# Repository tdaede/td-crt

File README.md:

# td-crt

This repo contains work-in-progress electronics to control a CRT monitor (aka a CRT chassis).

It is divided up into several separate projects, as follows:

* **[td-deflect](td-deflect/)** - Main PCB, containing microcontroller, horizontal and vertical deflection circuits, RGB amplifier, B+ power supply, 12V and -12V power supplies, and heater power supply. Functional with an enormous amount of rework.

* **[td-hv](td-hv/)** - Regulated HV/focus/screen power supply, based on K7000 clone flyback. Currently marginally functional, demos were done with the original monitor's HV.

* **[td-rgbinput](td-rgbinput/)** - Poorly named RGB amplifier that replaces the version on td-deflect, using more modern parts. Currently untested.

* **[td-180v](td-180v/)** - 180V (and heater) boost converter, designed to be installed on a neck board to provide an optional dedicated power supply for the cathode amplifiers.

* **[td-rgb](td-rgb/)** - Old RGB mod PCB, I should move it to a separate repo at some point.

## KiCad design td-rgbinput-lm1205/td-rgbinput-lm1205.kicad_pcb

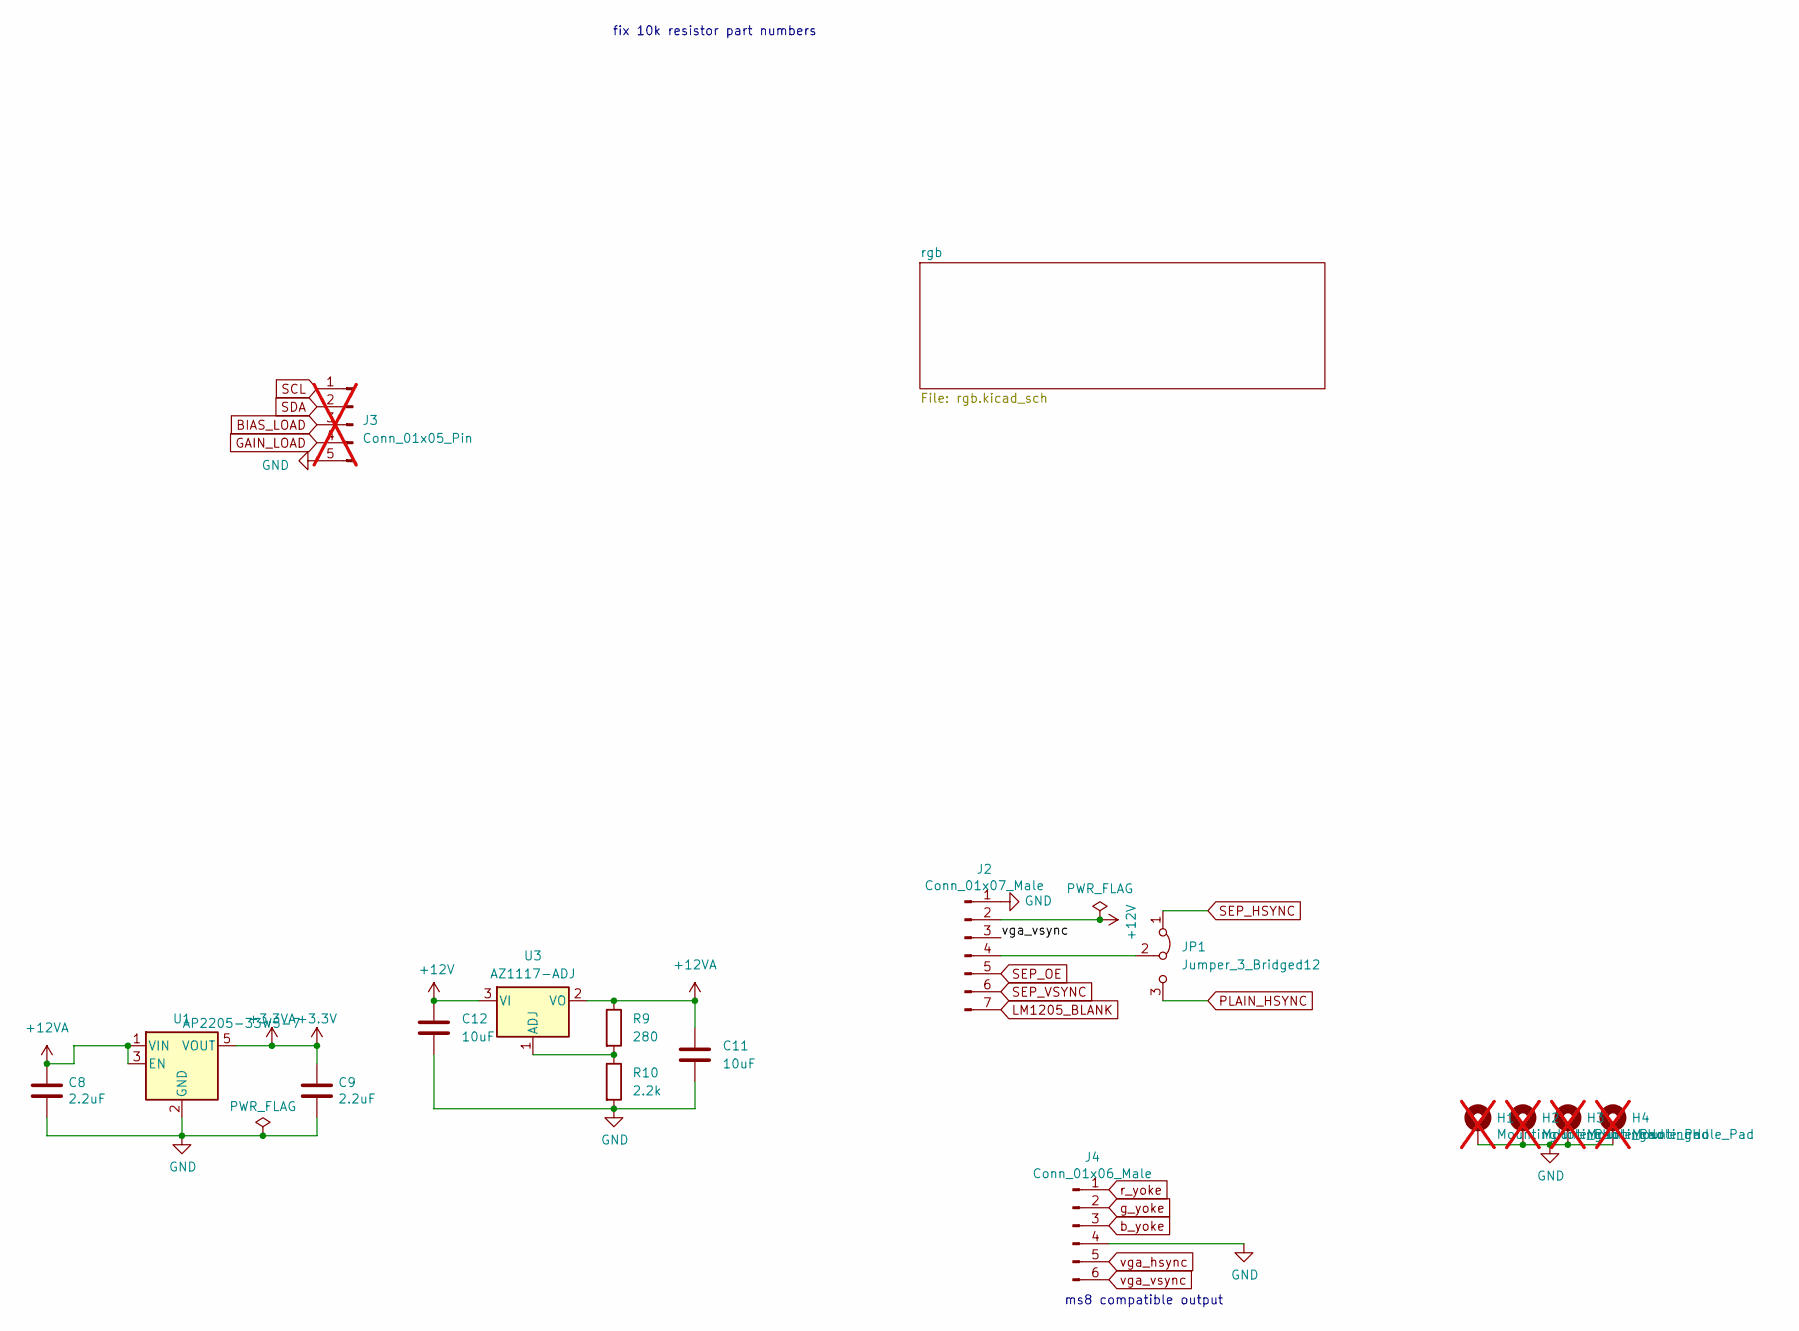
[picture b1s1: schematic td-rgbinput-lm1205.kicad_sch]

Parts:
C8, C9: 2.2uF; C_0805_2012Metric; Digikey 490-14467-1-ND
C11, C12: 10uF; C_0805_2012Metric; Digikey 490-10516-1-ND
H1, H2, H3, H4: MountingHole_Pad; MountingHole_3.2mm_M3_Pad_Via; not fitted
J2: Conn_01x07_Male; JST_XH_B7B-XH-A_1x07_P2.50mm_Vertical; Digikey 1175-51025-07-0100-01-ND
J3: Conn_01x05_Pin; JST_XH_B5B-XH-A_1x05_P2.50mm_Vertical; Digikey B5B-XH-A; not fitted
J4: Conn_01x06_Male; JST_EH_B6B-EH-A_1x06_P2.50mm_Vertical; Digikey 455-1615-ND
JP1: Jumper_3_Bridged12; PinHeader_1x03_P2.54mm_Vertical
R9: 280; R_0805_2012Metric; Digikey 311-280CRCT-ND
R10: 2.2k; R_0805_2012Metric; Digikey 311-2.20KCRCT-ND
U1: AP2205-33W5-7; SOT-23-5; Digikey 31-AP2205-33W5-7CT-ND
U3: AZ1117-ADJ; SOT-223-3_TabPin2; Digikey AZ1117CH-ADJTRG1DICT-ND

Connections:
+3.3V: C9.1, U1.5 (VOUT); also elsewhere on the board
+12V: C12.1, J2.2, U3.3 (VI)
+12VA: C8.1, C11.1, R9.1, U1.1 (VIN), U1.3 (EN), U3.2 (VO); also elsewhere on the board
BIAS_LOAD: J3.3; also elsewhere on the board
GAIN_LOAD: J3.4; also elsewhere on the board
GND: C8.2, C9.2, C11.2, C12.2, H1.1, H2.1, H3.1, H4.1, J2.1, J3.5, J4.4, R10.2, U1.2 (GND); also elsewhere on the board
LM1205_BLANK: J2.7; also elsewhere on the board
unnamed: J2.4, JP1.2 (C)
unnamed: R9.2, R10.1, U3.1 (ADJ)
PLAIN_HSYNC: JP1.3 (B); also elsewhere on the board
SCL: J3.1; also elsewhere on the board
SDA: J3.2; also elsewhere on the board
SEP_HSYNC: JP1.1 (A); also elsewhere on the board
SEP_OE: J2.5; also elsewhere on the board
SEP_VSYNC: J2.6; also elsewhere on the board
b_yoke: J4.3; also elsewhere on the board
g_yoke: J4.2; also elsewhere on the board
r_yoke: J4.1; also elsewhere on the board
vga_hsync: J4.5; also elsewhere on the board
vga_vsync: J2.3, J4.6; also elsewhere on the board

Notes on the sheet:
ms8 compatible output
fix 10k resistor part numbers

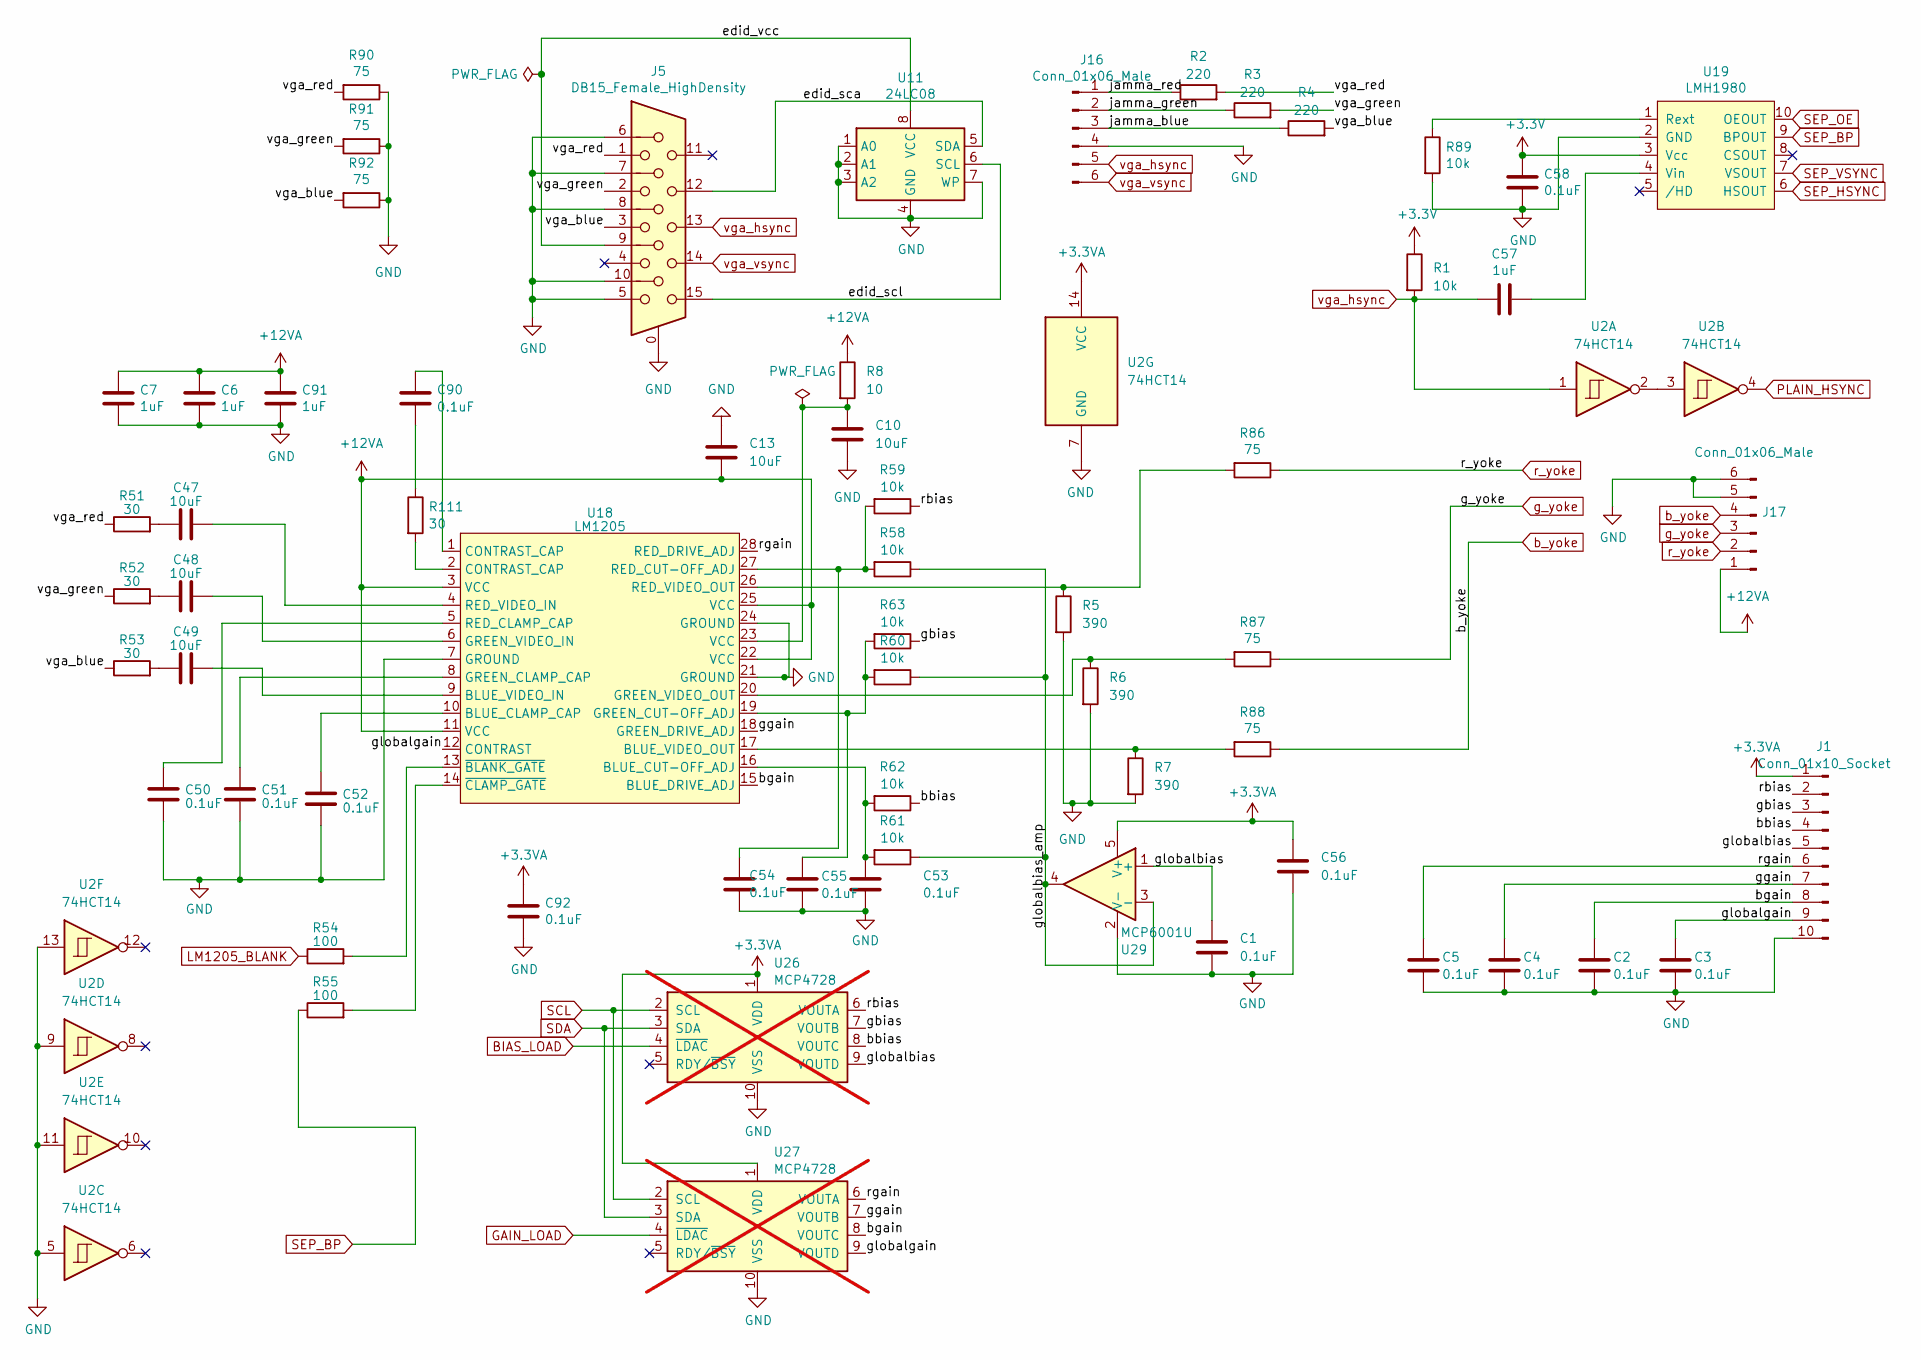
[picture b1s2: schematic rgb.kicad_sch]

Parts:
C1, C2, C3, C4, C5, C50, C51, C52, C53, C54, C55, C56, C58, C90, C92: 0.1uF; C_0805_2012Metric; Digikey 1276-1099-1-ND
C6, C7, C91: 1uF; C_0805_2012Metric; Digikey 1276-1066-1-ND
C10, C13, C47, C48, C49: 10uF; C_0805_2012Metric; Digikey 490-10516-1-ND
C57: 1uF; C_0805_2012Metric; Voltage 25V; Digikey 1276-1066-1-ND
J1: Conn_01x10_Socket; JST_XH_B10B-XH-A_1x10_P2.50mm_Vertical; Digikey 455-B10B-XH-A-ND
J5: DB15_Female_HighDensity; DSUB-15-HD_Socket_Horizontal_P2.29x2.54mm_EdgePinOffset8.35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; Digikey L77HDE15SD1CH4FVGA-ND
J16: Conn_01x06_Male; JST_EH_B6B-EH-A_1x06_P2.50mm_Vertical; Digikey 455-1615-ND
J17: Conn_01x06_Male; JST_XH_B6B-XH-A_1x06_P2.50mm_Vertical; Digikey 455-2271-ND
R1, R58, R59, R60, R61, R62, R63, R89: 10k; R_0805_2012Metric; Digikey 311-1.00KCRCT-ND
R2, R3, R4: 220; R_0805_2012Metric; Digikey 311-220CRCT-ND
R5, R6, R7: 390; R_0805_2012Metric; Digikey 311-390CRCT-ND
R8: 10; R_0805_2012Metric; Digikey 311-10.0CRCT-ND
R51, R52, R53, R111: 30; R_0805_2012Metric; Digikey 311-30.0CRCT-ND
R54, R55: 100; R_0805_2012Metric; Digikey 311-100CRCT-ND
R86, R87, R88, R90, R91, R92: 75; R_0805_2012Metric; Digikey 311-75.0CRCT-ND
U2: 74HCT14; SOIC-14_3.9x8.7mm_P1.27mm; Digikey 74HCT14S14-13DICT-ND
U11: 24LC08; SOIC-8_3.9x4.9mm_P1.27mm; Digikey 24LC08BT/SNCT-ND
U18: LM1205; DIP-28_W15.24mm; Digikey 3M5481-ND
U19: LMH1980; VSSOP-10_3x3mm_P0.5mm; Digikey LMH1980MM/NOPBCT-ND
U26, U27: MCP4728; MSOP-10_3x3mm_P0.5mm; Digikey MCP4728T-E/UNCT-ND; not fitted
U29: MCP6001U; SOT-23-5; Digikey MCP6001UT-I/OTCT-ND

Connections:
+3.3V: C56.1, C58.1, C92.1, J1.1, R1.1, U2.14 (VCC), U19.3 (Vcc), U26.1 (VDD), U27.1 (VDD), U29.5 (V+); also elsewhere on the board
+12VA: C6.1, C7.1, C13.1, C91.1, J17.1, R8.1, U18.3 (VCC), U18.11 (VCC), U18.22 (VCC), U18.25 (VCC); also elsewhere on the board
/rgb/bbias: J1.4, R62.1, U26.8 (VOUTC)
/rgb/bgain: C2.1, J1.8, U18.15 (BLUE_DRIVE_ADJ), U27.8 (VOUTC)
/rgb/edid_sca: J5.12, U11.5 (SDA)
/rgb/edid_scl: J5.15, U11.6 (SCL)
/rgb/edid_vcc: J5.9, U11.8 (VCC)
/rgb/gbias: J1.3, R63.1, U26.7 (VOUTB)
/rgb/ggain: C4.1, J1.7, U18.18 (GREEN_DRIVE_ADJ), U27.7 (VOUTB)
/rgb/globalbias: C1.1, J1.5, U26.9 (VOUTD), U29.1 (+)
/rgb/globalbias_amp: R58.1, R60.1, R61.1, U29.3 (-), U29.4
/rgb/globalgain: C3.1, J1.9, U18.12 (CONTRAST), U27.9 (VOUTD)
/rgb/jamma_blue: J16.3, R4.1
/rgb/jamma_green: J16.2, R3.1
/rgb/jamma_red: J16.1, R2.1
/rgb/rbias: J1.2, R59.1, U26.6 (VOUTA)
/rgb/rgain: C5.1, J1.6, U18.28 (RED_DRIVE_ADJ), U27.6 (VOUTA)
/rgb/vga_blue: J5.3, R4.2, R53.1, R92.2
/rgb/vga_green: J5.2, R3.2, R52.1, R91.2
/rgb/vga_red: J5.1, R2.2, R51.1, R90.2
BIAS_LOAD: U26.4 (~LDAC); also elsewhere on the board
GAIN_LOAD: U27.4 (~LDAC); also elsewhere on the board
GND: C1.2, C2.2, C3.2, C4.2, C5.2, C6.2, C7.2, C10.2, C13.2, C50.1, C51.1, C52.1, C53.2, C54.2, C55.2, C56.2, C58.2, C91.2, C92.2, J1.10, J5.0, J5.5, J5.6, J5.7, J5.8, J5.10, J16.4, J17.5, J17.6, R5.2, R6.2, R7.2, R89.2, R90.1, R91.1, R92.1, U2.5, U2.7 (GND), U2.9, U2.11, U2.13, U11.1 (A0), U11.2 (A1), U11.3 (A2), U11.4 (GND), U11.7 (WP), U18.7 (GROUND), U18.21 (GROUND), U18.24 (GROUND), U19.2 (GND), U26.10 (VSS), U27.10 (VSS), U29.2 (V-); also elsewhere on the board
LM1205_BLANK: R54.1; also elsewhere on the board
unnamed: C10.1, R8.2, U18.23 (VCC)
unnamed: C47.1, R51.2
unnamed: C48.1, R52.2
unnamed: C49.1, R53.2
unnamed: C90.1, U18.1 (CONTRAST_CAP)
unnamed: C90.2, R111.1
unnamed: R111.2, U18.2 (CONTRAST_CAP)
unnamed: U2.2, U2.3
unnamed: C52.2, U18.10 (BLUE_CLAMP_CAP)
unnamed: C53.1, R61.2, R62.2, U18.16 (BLUE_CUT-OFF_ADJ)
unnamed: C49.2, U18.9 (BLUE_VIDEO_IN)
unnamed: R7.1, R88.2, U18.17 (BLUE_VIDEO_OUT)
unnamed: C51.2, U18.8 (GREEN_CLAMP_CAP)
unnamed: C55.1, R60.2, R63.2, U18.19 (GREEN_CUT-OFF_ADJ)
unnamed: C48.2, U18.6 (GREEN_VIDEO_IN)
unnamed: R6.1, R87.2, U18.20 (GREEN_VIDEO_OUT)
unnamed: C50.2, U18.5 (RED_CLAMP_CAP)
unnamed: C54.1, R58.2, R59.2, U18.27 (RED_CUT-OFF_ADJ)
unnamed: C47.2, U18.4 (RED_VIDEO_IN)
unnamed: R5.1, R86.2, U18.26 (RED_VIDEO_OUT)
unnamed: R54.2, U18.13 (~BLANK_GATE)
unnamed: R55.2, U18.14 (~CLAMP_GATE)
unnamed: R89.1, U19.1 (Rext)
unnamed: C57.1, U19.4 (Vin)
PLAIN_HSYNC: U2.4; also elsewhere on the board
SCL: U26.2 (SCL), U27.2 (SCL); also elsewhere on the board
SDA: U26.3 (SDA), U27.3 (SDA); also elsewhere on the board
SEP_BP: R55.1, U19.9 (BPOUT)
SEP_HSYNC: U19.6 (HSOUT); also elsewhere on the board
SEP_OE: U19.10 (OEOUT); also elsewhere on the board
SEP_VSYNC: U19.7 (VSOUT); also elsewhere on the board
b_yoke: J17.4, R88.1; also elsewhere on the board
g_yoke: J17.3, R87.1; also elsewhere on the board
r_yoke: J17.2, R86.1; also elsewhere on the board
vga_hsync: C57.2, J5.13, J16.5, R1.2, U2.1; also elsewhere on the board
vga_vsync: J5.14, J16.6; also elsewhere on the board

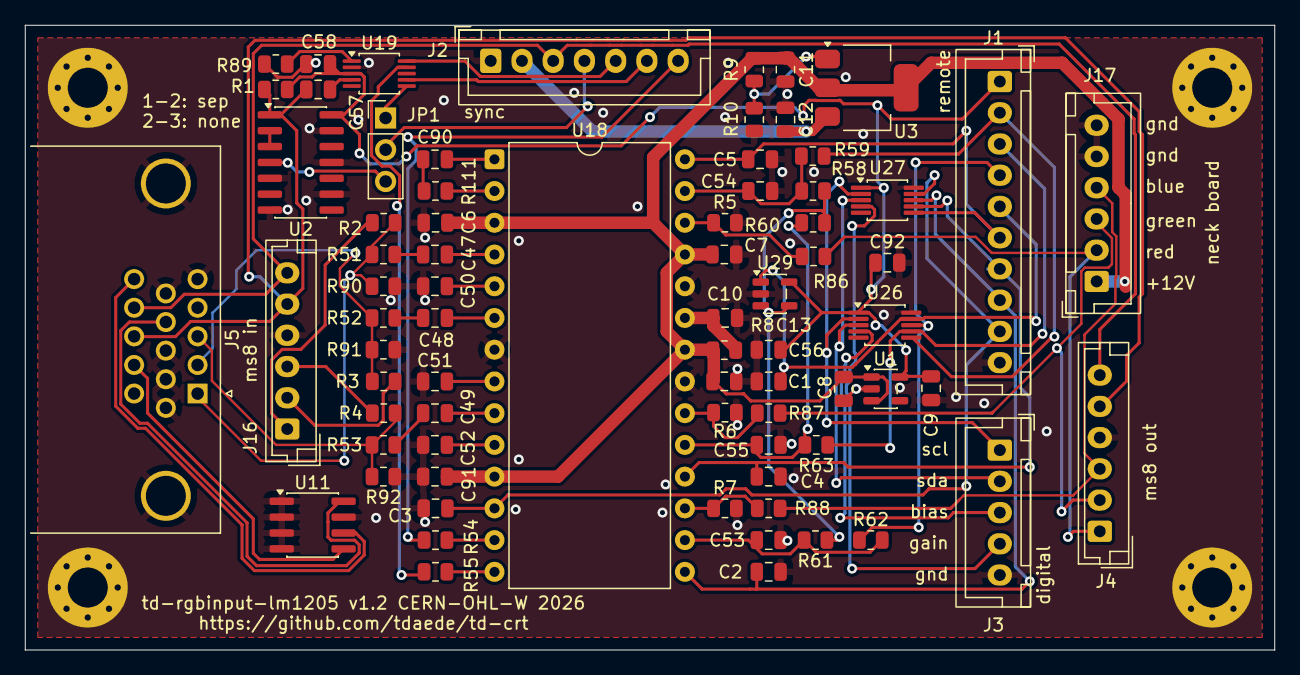
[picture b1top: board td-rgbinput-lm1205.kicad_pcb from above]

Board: 2 copper layers, 100.0 x 50.0 mm, 78 parts (0 on the bottom side), 63 nets.

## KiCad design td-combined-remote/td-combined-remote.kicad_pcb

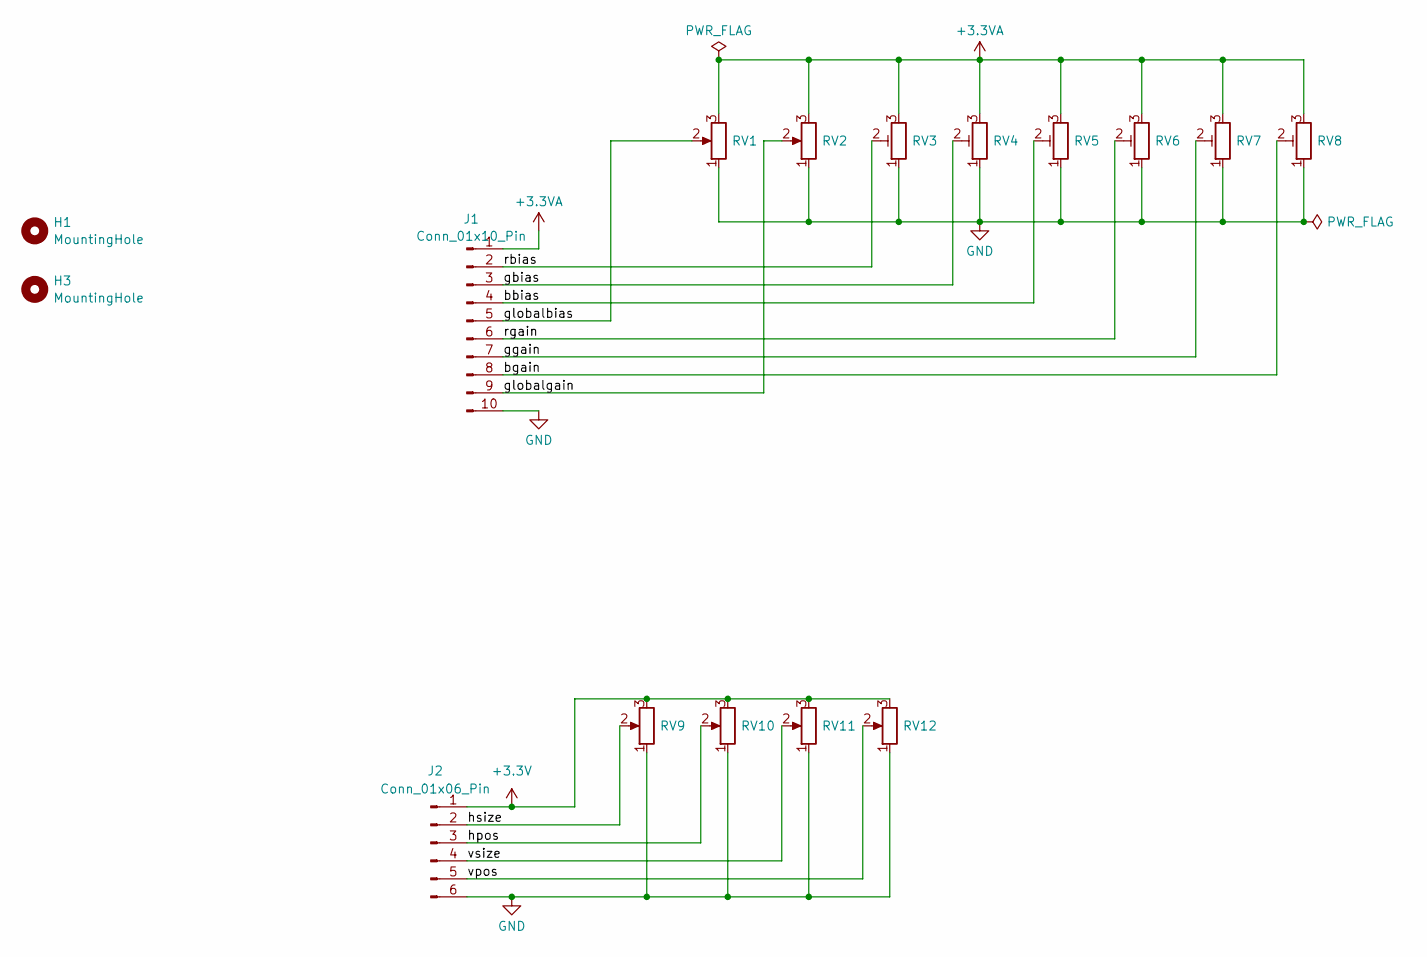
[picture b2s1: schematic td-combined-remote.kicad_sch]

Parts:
H1, H3: MountingHole; MountingHole_3.2mm_M3
J1: Conn_01x10_Pin; JST_XH_S10B-XH-A_1x10_P2.50mm_Horizontal; Digikey 455-S10B-XH-A-ND
J2: Conn_01x06_Pin; JST_XH_S6B-XH-A_1x06_P2.50mm_Horizontal; Digikey 455-S6B-XH-A-ND
RV1, RV2, RV9, RV10, RV11, RV12: R_Potentiometer; Potentiometer_Alps_RK09K_Single_Vertical; Digikey PTV09A-4015U-B103-ND
RV3, RV4, RV5, RV6, RV7, RV8: R_Potentiometer_Trim; Potentiometer_Bourns_3386P_Vertical; Digikey 3386P-103TLF-ND

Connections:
+3.3V: J2.1, RV9.3, RV10.3, RV11.3, RV12.3
+3.3VA: J1.1, RV1.3, RV2.3, RV3.3, RV4.3, RV5.3, RV6.3, RV7.3, RV8.3
/bbias: J1.4, RV5.2
/bgain: J1.8, RV8.2
/gbias: J1.3, RV4.2
/ggain: J1.7, RV7.2
/globalbias: J1.5, RV1.2
/globalgain: J1.9, RV2.2
/hpos: J2.3, RV10.2
/hsize: J2.2, RV9.2
/rbias: J1.2, RV3.2
/rgain: J1.6, RV6.2
/vpos: J2.5, RV12.2
/vsize: J2.4, RV11.2
GND: J1.10, J2.6, RV1.1, RV2.1, RV3.1, RV4.1, RV5.1, RV6.1, RV7.1, RV8.1, RV9.1, RV10.1, RV11.1, RV12.1

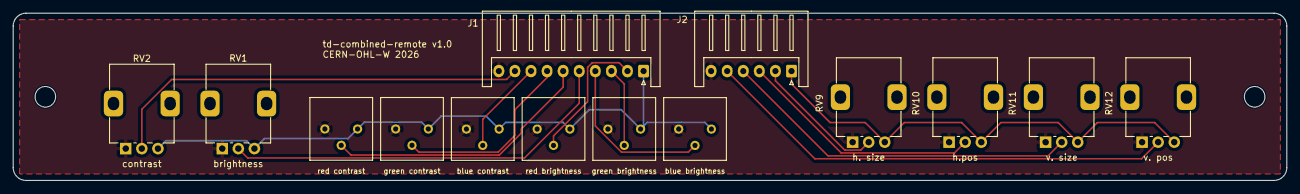
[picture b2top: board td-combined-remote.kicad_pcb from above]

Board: 2 copper layers, 198.0 x 26.0 mm, 16 parts (0 on the bottom side), 15 nets.

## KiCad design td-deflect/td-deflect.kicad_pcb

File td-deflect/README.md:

**td-deflect** is the primary PCB of td-crt, containing most of the pieces of a complete chassis.

The chassis is a multisync design with separate HV and deflection, allowing arbitrary scan rates, within the voltage and current limits of the ciruit.

RGB input
---------

There is a completely analog RGB path, based on a M51387P RGB amplifier IC. While effective, the chip has been out of production for a long time and therefore the **td-rgbinput** board exists as a future design that eliminates the IC.

Sync processing
---------------

The sync is separated by a LMH1980 sync separator IC. This is responsible for AC coupling the sync input, and separating it into separate H and V syncs (in the case of composite sync). It is also relied on for the back porch output, which is fed in to the clamping circuts, and the odd/even output, which is used for interlacing support.

Horizontal PLL
--------------

There is no analog horizontal PLL - instead, the horizontal sync is fed directly into the timers of the STM32F7. A software PLL is implemented using the internal timers. While this leads to quite robust sync processing, it also results in a minimum PLL jitter of a single clock period of 4.6ns. This is adequate for 15kHz content but not ideal. A future board may use the STM32G4 instead, which has an internal DLL that leads to minimum jitter on the order of 184ps.

Vertical ramp generator
-----------------------

The vertical ramp is generated in software. A software correction is applied for linearity, after which it is output via the stm32's DAC.

Vertical amplifier
------------------

The vertical amplifier is a classic discrete class AB amp, with current feedback (a voltage input corresponds to a current setpoint). The feedback network is fixed in analog components, which turns out not to be flexible enough for all yoke designs. In addition, it does not actually have any AB biasing, instead relying on feedback to avoid crossover distortion, which limits its performance. That said, it's quite effective as is. The amplifer is DC-coupled so that vertical position offsets are simply a DC bias on the input.

One leg of the amplifier is powered by 12V, and the other is powered by 48V in order to provide a faster retrace interval with high inductance yokes.

A planned future design replaces the vertical amplifier with a class D circuit with software feedback, to allow software tuning of the feedback network as well as increased power efficiency, though with the added complexity of dampled RLC output filter design.

Horizontal circuit
------------------

The horizontal circuit is a classic CRT horizontal class-C amplifier, which recovers the energy stored in the yoke for retrace.

The horizontal output transistor is a silicon carbide MOSFET for its very high voltage handling abilities. BJT-based HOTs are still manufactured as a backup option, however SiC MOSFETs are actually cheaper now and offer better performance. In addition, their intrinisic body diode renders an external freewheeling diode unnecessary.

A fixed film cap is used as the retrace timing capacitor.

There is a bank of 4 switchable S-capacitors allowing for 16 total possible S correction values.

There is no E-W correction or horizontal DC bias adjustment.

There is a current sense transformer provided for current feedback, but it is currently untested.

B+ power supply
---------------

The B+ power supply is a 100-200V boost converter to power the horizontal deflection circuits. It is based on a LT3758A asynchronous boost controller and is capable of up to 500mA of output current. It is currently thermally limited and could use a bit of work to increase efficiency and therefore boost the output power.

12V power supply
----------------

There is a 12V buck converter for 12V.

Negative 12V power supply
-----------------

There is a boost topology -12V converter. It currently does not work.

Heater power supply
-------------------

A linear regulator provides a heater power supply. Untested.

HV circuit
----------

Part of an extremely basic HV driver is present on the PCB, but is untested.

Software
--------

The on-board STM32 handles horizontal and vertical deflection, though the rest of the board runs without software intervention. The software is based on the [RTIC](https://rtic.rs) framework and written in Rust. It provides a very primitive serial interface to upload configuration and download runtime statistics. The software is also responsible for implementing all of the self protection logic.

There is a companion desktop GTK4 app with an extremely basic "remote" GUI.

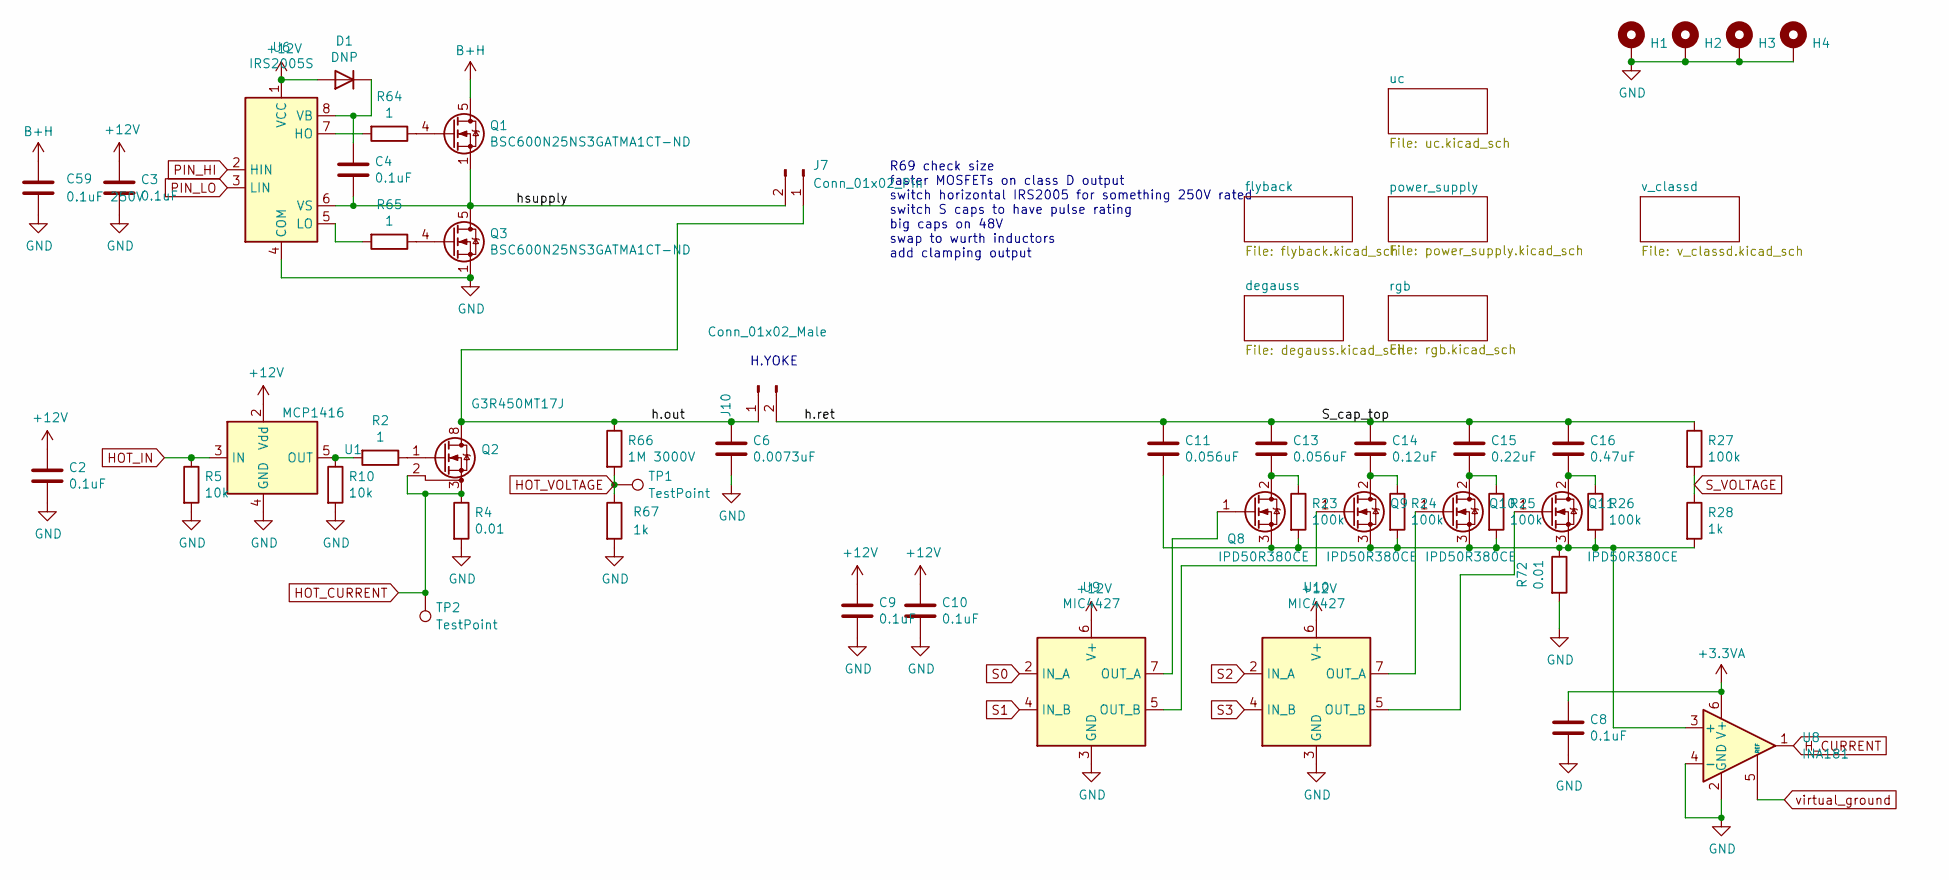
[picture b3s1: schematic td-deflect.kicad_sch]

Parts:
C2, C3, C4: 0.1uF; C_0805_2012Metric_Pad1.18x1.45mm_HandSolder; Digikey 311-1140-1-ND
C6: 0.0073uF; C_Rect_L18.0mm_W6.0mm_P15.00mm_FKS3_FKP3; Voltage 2000V; Digikey 495-3231-ND
C8, C9, C10: 0.1uF; C_0805_2012Metric_Pad1.18x1.45mm_HandSolder; Voltage 10V; Digikey 311-1140-1-ND
C11, C13: 0.056uF; C_Rect_L18.0mm_W5.0mm_P15.00mm_FKS3_FKP3; Voltage 250V; Digikey 732-5795-ND
C14: 0.12uF; C_Rect_L18.0mm_W8.0mm_P15.00mm_FKS3_FKP3; Voltage 250V; Digikey 732-5799-ND
C15: 0.22uF; C_Rect_L18.0mm_W6.0mm_P15.00mm_FKS3_FKP3; Voltage 250V; Digikey 732-5802-ND
C16: 0.47uF; C_Rect_L18.0mm_W8.0mm_P15.00mm_FKS3_FKP3; Voltage 250V; Digikey 732-5805-ND
C59: 0.1uF 250V; C_1206_3216Metric; Digikey 445-8899-1-ND
D1: DNP; D_SOD-123; Digikey ES1G-FDICT-ND
H1, H2, H3, H4: MountingHole_Pad; MountingHole_3.2mm_M3_Pad_Via; Digikey DNP
J7: Conn_01x02_Pin; monitor_10_8_2p
J10: Conn_01x02_Male; monitor_10_8_2p; Digikey DNP
Q1, Q3: BSC600N25NS3GATMA1CT-ND; TDSON-8-1; Digikey BSC600N25NS3GATMA1CT-ND
Q2: G3R450MT17J; TO-263-7_TabPin8_GeneSiC; Digikey 1242-G3R450MT17J-TRCT-ND
Q8, Q9, Q10, Q11: IPD50R380CE; TO-252-2; Digikey IPD50R380CEAUMA1CT-ND
R2, R64, R65: 1; R_0805_2012Metric_Pad1.20x1.40mm_HandSolder; Digikey 311-1.00CRCT-ND
R4, R72: 0.01; R_0805_2012Metric_Pad1.20x1.40mm_HandSolder; Digikey 311-0.01NUCT-ND
R5, R10: 10k; R_0805_2012Metric_Pad1.20x1.40mm_HandSolder; Digikey 311-10.0KCRCT-ND
R23, R24, R25, R26: 100k; R_1206_3216Metric_Pad1.30x1.75mm_HandSolder; Digikey 311-100KFRCT-ND
R27: 100k; R_1206_3216Metric_Pad1.30x1.75mm_HandSolder; Voltage 200V; Digikey 311-100KFRCT-ND
R28: 1k; R_1206_3216Metric_Pad1.30x1.75mm_HandSolder; Voltage 200V; Digikey 311-1.00KFRCT-ND
R66: 1M 3000V; R_2512_6332Metric; Digikey CHV2512-FX-1004ELFCT-ND
R67: 1k; R_0805_2012Metric_Pad1.20x1.40mm_HandSolder; Digikey 311-1.00KCRCT-ND
TP1, TP2: TestPoint; TestPoint_Keystone_5015_Micro_Mini; Digikey 36-5015CT-ND
U1: MCP1416; SOT-23-5; Digikey MCP1416T-E/OTCT-ND
U6: IRS2005S; SOIC-8_3.9x4.9mm_P1.27mm; Digikey IRS2005STRPBFCT-ND
U8: INA181; SOT-23-6; Digikey 296-47658-1-ND
U9, U10: MIC4427; SOIC-8_3.9x4.9mm_P1.27mm; Digikey 576-1525-5-ND

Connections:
+3.3VA: C8.1, U8.6 (V+); also elsewhere on the board
+12V: C2.1, C3.1, C9.1, C10.1, D1.2 (A), U1.2 (Vdd), U6.1 (VCC), U9.6 (V+), U10.6 (V+); also elsewhere on the board
/S_cap_top: C11.1, C13.1, C14.1, C15.1, C16.1, J10.2, R27.1
/h.out: C6.1, J7.1, J10.1, Q2.8 (D), R66.1
/hsupply: C4.2, J7.2, Q1.1 (S), Q1.2 (S), Q1.3 (S), Q3.5 (D), U6.6 (VS)
B+H: C59.1, Q1.5 (D); also elsewhere on the board
GND: C2.2, C3.2, C6.2, C8.2, C9.2, C10.2, C59.2, H1.1, H2.1, H3.1, H4.1, Q3.1 (S), Q3.2 (S), Q3.3 (S), R4.2, R5.2, R10.2, R67.2, R72.2, U1.4 (GND), U6.4 (COM), U8.2 (GND), U8.4 (-), U9.3 (GND), U10.3 (GND); also elsewhere on the board
HOT_CURRENT: Q2.2 (DS), Q2.3 (S), Q2.4 (S), Q2.5 (S), Q2.6 (S), Q2.7 (S), R4.1, TP2.1; also elsewhere on the board
HOT_IN: R5.1, U1.3 (IN); also elsewhere on the board
HOT_VOLTAGE: R66.2, R67.1, TP1.1
H_CURRENT: U8.1; also elsewhere on the board
unnamed: C4.1, D1.1 (K), U6.8 (VB)
unnamed: Q1.4 (G), R64.1
unnamed: Q2.1 (G), R2.1
unnamed: Q3.4 (G), R65.1
unnamed: C13.2, Q8.2 (D), R23.1
unnamed: Q8.1 (G), U9.7 (OUT_A)
unnamed: C14.2, Q9.2 (D), R24.1
unnamed: Q9.1 (G), U9.5 (OUT_B)
unnamed: C15.2, Q10.2 (D), R25.1
unnamed: Q10.1 (G), U10.7 (OUT_A)
unnamed: C11.2, Q8.3 (S), Q9.3 (S), Q10.3 (S), Q11.3 (S), R23.2, R24.2, R25.2, R26.2, R28.2, R72.1, U8.3 (+)
unnamed: C16.2, Q11.2 (D), R26.1
unnamed: Q11.1 (G), U10.5 (OUT_B)
unnamed: R2.2, R10.1, U1.5 (OUT)
unnamed: R64.2, U6.7 (HO)
unnamed: R65.2, U6.5 (LO)
PIN_HI: U6.2 (HIN); also elsewhere on the board
PIN_LO: U6.3 (LIN); also elsewhere on the board
S0: U9.2 (IN_A); also elsewhere on the board
S1: U9.4 (IN_B); also elsewhere on the board
S2: U10.2 (IN_A); also elsewhere on the board
S3: U10.4 (IN_B); also elsewhere on the board
S_VOLTAGE: R27.2, R28.1; also elsewhere on the board
virtual_ground: U8.5 (REF); also elsewhere on the board

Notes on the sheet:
H.YOKE
R69 check size faster MOSFETs on class D output switch horizontal IRS2005 for something 250V rated switch S caps to have pulse rating big caps on 48V swap to wurth inductors add clamping output

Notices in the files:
td-bplus-psu-gan/td-bplus-psu-gan.kicad_pcb:
CERN-OHL-W 2024
td-bplus-psu/td-bplus-psu.kicad_pcb:
CERN-OHL-W 2025
td-combined-remote/td-combined-remote.kicad_pcb:
CERN-OHL-W 2026
td-hv/td-hv.kicad_pcb:
td-hv v2.1 CERN OHL-W 2025
td-rgbinput-lm1205/td-rgbinput-lm1205.kicad_pcb:
td-rgbinput-lm1205 v1.2 CERN-OHL-W 2026
